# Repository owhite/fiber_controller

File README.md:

# fiber_controller

### **Collision protection**

* Raytools BM110/BM111 "Collision Protection" Kit

* BM111 have a specific internal magnetic sensor and a sacrificial ceramic assembly, but Raytools also offers an external 3D collision mount for high-end machines.  
* [Raytools TRA Nozzle Assembly](https://raytools.vn/product/raytools-original-tra-nozzle-assembly-for-bm111-bm110-laser-cutting-head/)  
* [Raytools 3d head sensor](https://www.amazon.com/Raytools-Head-Capacitive-Sensor-Connector/dp/B0FQ5VNJ7H?th=1) 
* Sacrificial Ceramic Rings If a full magnetic mount is too bulky for your Z-axis design, you should rely on the ceramic ring. For 1.5kW, this is the standard point of failure. [Original Raytools Ceramic Rings (AliExpress)](https://www.aliexpress.com/i/4000780398952.html)

FreeMascot 1064nm Safety Glasses

### **LinuxCNC stack**

* [QtPlasmaC](https://linuxcnc.org/docs/html/plasma/qtplasmac.html)  
* Mesa [7i96S](https://store.mesanet.com/index.php?route=product/product&product_id=374) (or 7i76E)  
* [THCAD-10](https://store.mesanet.com/index.php?route=product/product&product_id=127) height sensing

### **Controller box**

* [Raycus RFL-C1500 User Guide](https://en.raycuslaser.com/upload/20220324/1futhmi6h1r9g1vrto.pdf)  
* [Maxphotonics MFSC 1000W-1500W Manual](https://pdf.directindustry.com/pdf/maxphotonics-co-ltd/mfp-series-q-switched-pulse-fiber-laser-user-s-guide/157735-629681.html): If cloudraw source uses the Maxphotonics "G3" architecture, this manual provides the specific 8-bit power bus logic (Pins 1-8).

### **Laser side signal condition on DB-25**

* Modulation (Pin 19): Use an RS-422 Differential Receiver to maintain a crisp 20kHz pulse and block EMI over the long cable run.  
* Power Supply: Tap Pin 17 (+5V) on the laser's DB25 to power your buffer circuit (verify voltage with a multimeter first).  
* Grounding: Use Pin 25 (GND) as your logic common; ensure the cable shield is grounded at the laser end only.  
* Safety Isolation: Use Optoisolators for low-speed logic (Enable, Ready, Error) to protect the Mesa board from high-voltage faults.  
* Hardware: House the circuit in a shielded aluminum box mounted directly to the laser using a DB25 Male-to-Male gender changer.  
* Cable Quality: Deploy a double-shielded industrial DB25 cable (foil \+ braid) to act as a barrier against servo motor noise.

### **DIN rail systems**

* 24V Field Power system, Mean Well [SDR-120-24](https://mou.sr/4vt2Dxf)  
* General purpose relay [38.52.7.024.0050](https://www.digikey.com/en/products/detail/finder-relays-inc/38.52.7.024.0050/10055815) and socket 93.02.7.024  
* [Narrow Slot Wire Duct](https://google.com/search?q=\(1%22+W+x+3%22+H\)+-+Black+Narrow+Slot+Wire+Duct+6.5%27&prds=headlineOfferDocid%3A3394051378468670811%2Cproductid%3A3394051378468670811%2Cpvo%3A38%2Cpvt%3Ahg&ibp=oshop&pvo=38&opi=103135050&gl=US&hl=en&noiga=1)  
* [Push-In Terminal Blocks](https://google.com/search?q=10pcs/set+PT+2.5+Push-In+Din+Rail+Mounted+Terminal+Blocks+Spring+Screwless+Feed,+Size:+24,+Gray&prds=headlineOfferDocid%3A9693193005356797468%2Cproductid%3A9693193005356797468%2Cpvo%3A38%2Cpvt%3Ahg&ibp=oshop&pvo=38&opi=103135050&gl=US&hl=en&noiga=1)  
* [Grounding Terminal Blocks](https://google.com/search?q=Siemens+Ground+Terminal+Block&prds=catalogid%3A8330128584833181567%2Cgpcid%3A10243653714409647064%2CheadlineOfferDocid%3A14112956594196320175%2Cmid%3A576462728235596048%2Cproductid%3A7214032751195772387%2Cpvo%3A38%2Cpvt%3Ahg&ibp=oshop&pvo=38&opi=103135050&gl=US&hl=en&noiga=1)

### **Height sensing:**

* Preamplifier (BCL-AMP), Converts capacitance to 0-10V for the THCAD.  
* Ceramic Ring, Isolates the nozzle to act as a sensor.  
* Shielded Coax Cable, Connects nozzle to Preamplifier.  
* Isolated 24V PSU, Eliminates signal noise from the 1.5kW source.

### **Chiller**

* The  [**S\&A CWFL-1500**](https://google.com/search?q=S%26A+CWFL-1500+Industrial+Water+Chiller+For+1500W+Fiber+Laser+Cutting+Machine&prds=headlineOfferDocid%3A17375003498786172168%2Cproductid%3A17375003498786172168%2Cpvo%3A38%2Cpvt%3Ahg&ibp=oshop&pvo=38&opi=103135050&gl=US&hl=en&noiga=1) dual circuit chiller

### **Gas control**

* gas control [system](https://alleriastore.com/products/auxiliary-gas-control-system)

* [Travis Mitchell](https://www.patreon.com/DIYfiberlaser) patreon site has a bill of materials

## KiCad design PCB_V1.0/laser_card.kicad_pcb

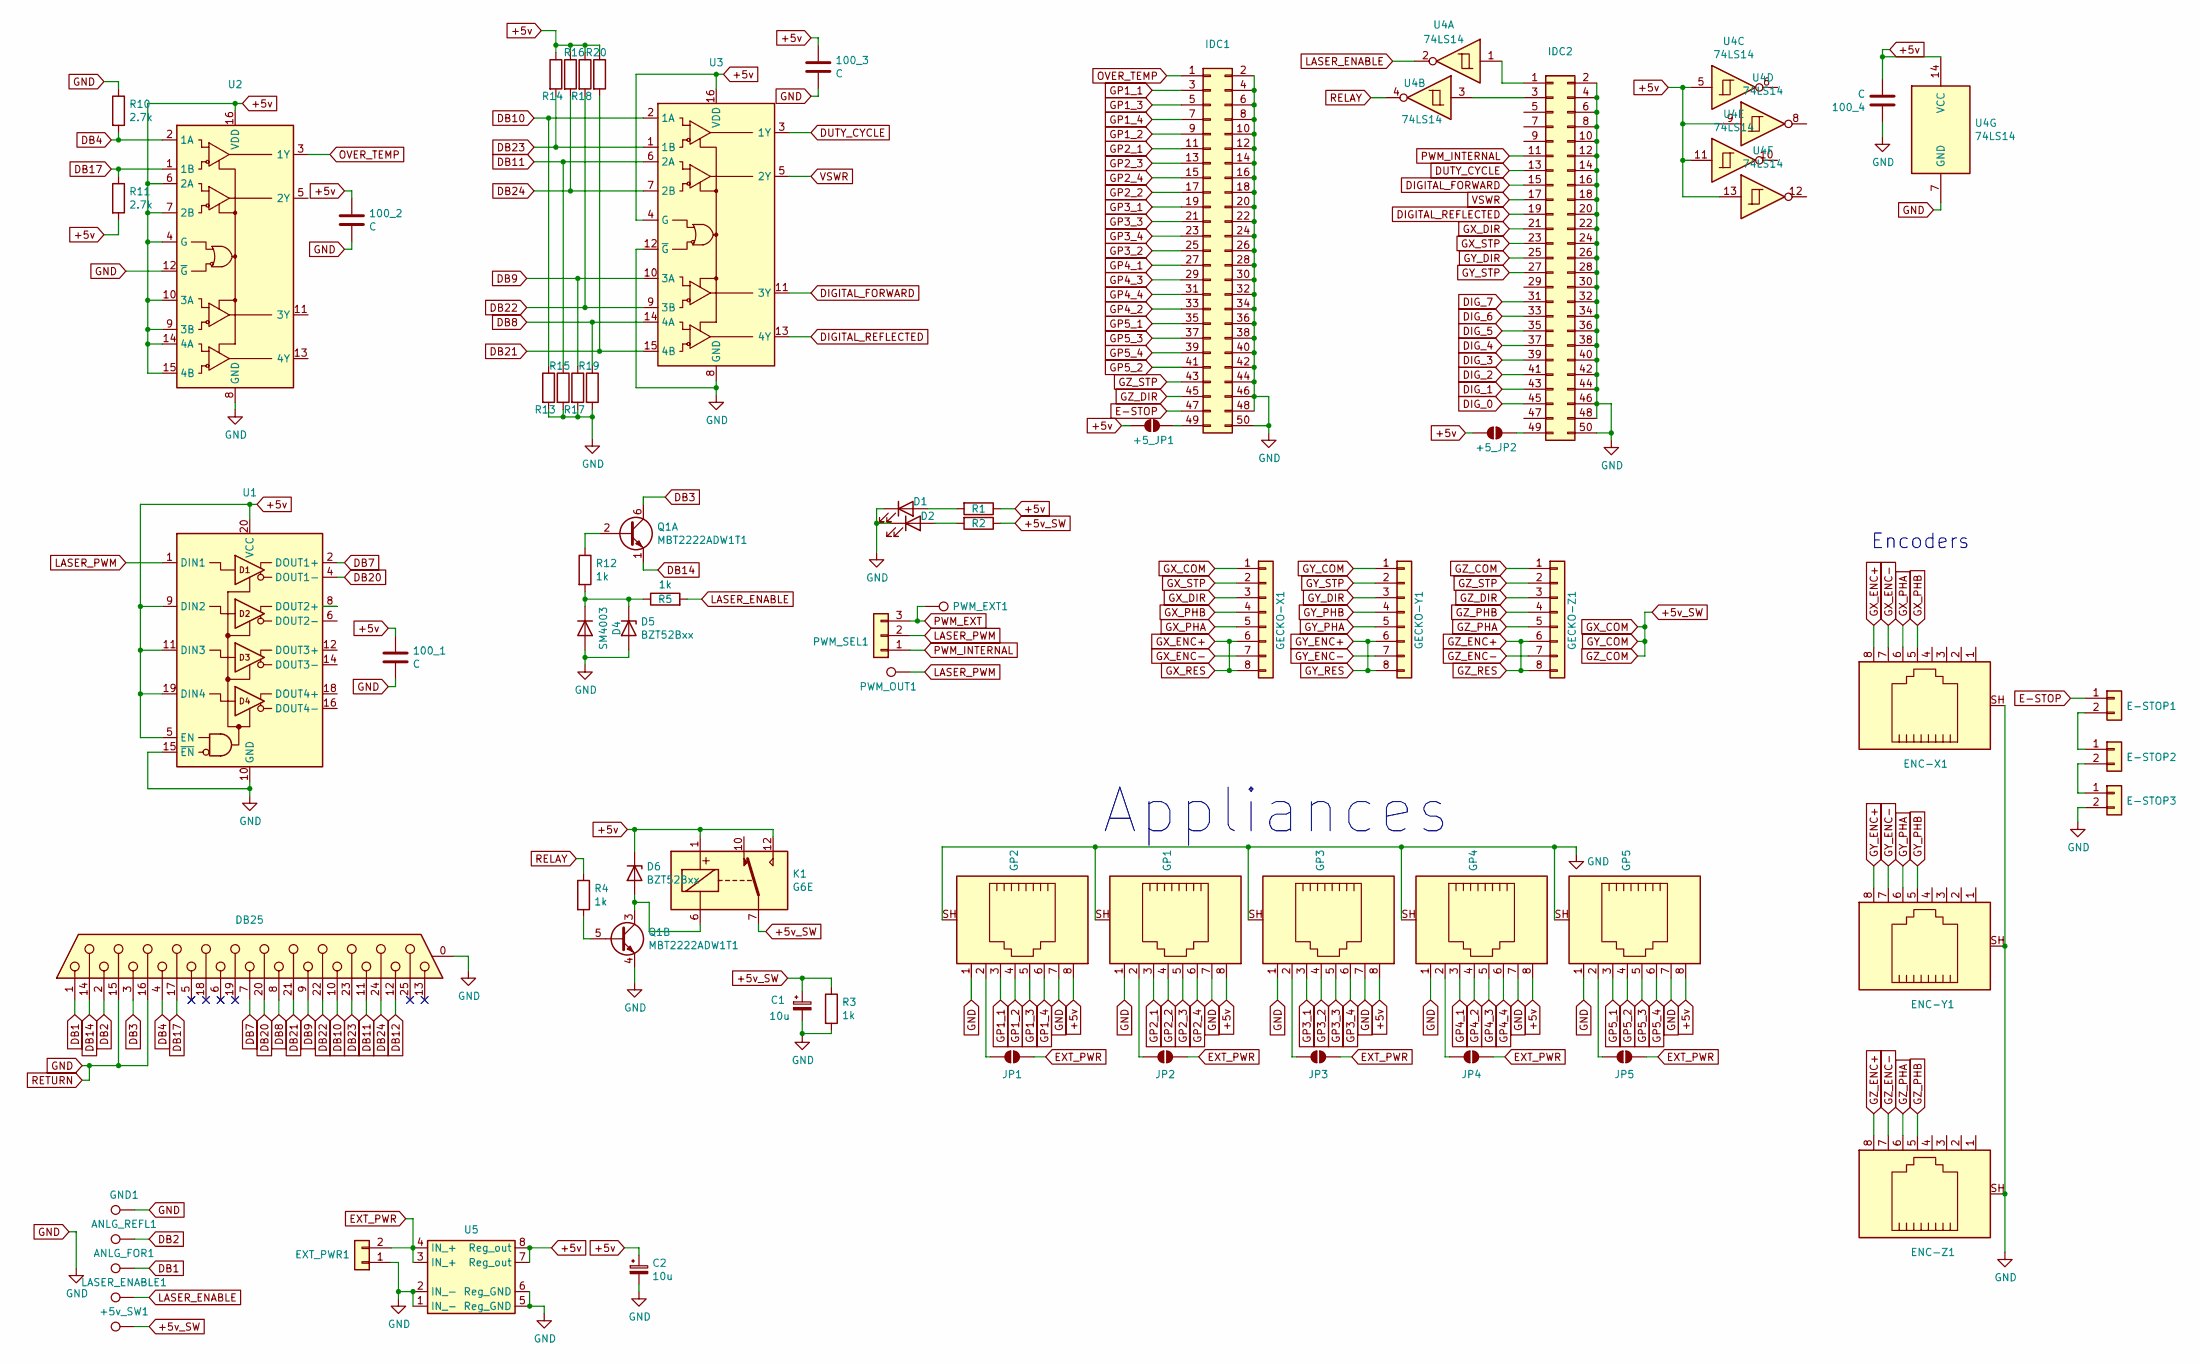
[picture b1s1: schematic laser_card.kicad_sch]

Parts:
100_1, 100_2, 100_3, 100_4: C; C_0805_2012Metric
+5_JP1, +5_JP2: SolderJumper_2_Open; SolderJumper-2_P1.3mm_Open_RoundedPad1.0x1.5mm
+5v_SW1: TestPoint; TestPoint_THTPad_2.0x2.0mm_Drill1.0mm
ANLG_FOR1: TestPoint; TestPoint_THTPad_2.0x2.0mm_Drill1.0mm
ANLG_REFL1: TestPoint; TestPoint_THTPad_2.0x2.0mm_Drill1.0mm
C1, C2: 10u; CP_Radial_D6.3mm_P2.50mm
D1, D2: LED; LED_0805_2012Metric
D4: SM4003; D_SOD-123F
D5, D6: BZT52Bxx; D_SOD-123
DB25: DB25_Female_MountingHoles; DSUB-25_Female_Vertical_P2.77x2.84mm_MountingHoles
E-STOP1, E-STOP2, E-STOP3: Conn_01x02; PinHeader_1x02_P2.54mm_Vertical
ENC-X1: RJ45_Shielded; my_RJ45_Amphenol
ENC-Y1: RJ45_Shielded; my_RJ45_Amphenol
ENC-Z1: RJ45_Shielded; my_RJ45_Amphenol
EXT_PWR1: Conn_01x02; PinHeader_1x02_P2.54mm_Vertical
GECKO-X1: molex; PinHeader_1x08_P2.54mm_Vertical
GECKO-Y1: molex; PinHeader_1x08_P2.54mm_Vertical
GECKO-Z1: molex; PinHeader_1x08_P2.54mm_Vertical
GND1: TestPoint; TestPoint_THTPad_2.0x2.0mm_Drill1.0mm
GP1, GP2, GP3, GP4, GP5: RJ45_Shielded; my_RJ45_Amphenol
IDC1, IDC2: Conn_02x25_Odd_Even; IDC-Header_2x25_P2.54mm_Vertical
JP1, JP2, JP3, JP4, JP5: SolderJumper_2_Open; SolderJumper-2_P1.3mm_Open_RoundedPad1.0x1.5mm
K1: G6E; Relay_SPDT_Omron_G6E
LASER_ENABLE1: TestPoint; TestPoint_THTPad_2.0x2.0mm_Drill1.0mm
PWM_EXT1: TestPoint; TestPoint_THTPad_2.0x2.0mm_Drill1.0mm
PWM_OUT1: TestPoint; TestPoint_THTPad_1.5x1.5mm_Drill0.7mm
PWM_SEL1: Conn_01x03; PinHeader_1x03_P2.54mm_Vertical
Q1: MBT2222ADW1T1; SOT-363_SC-70-6
R1, R2: 10k; R_0805_2012Metric
R3, R4, R5, R12: 1k; R_0805_2012Metric
R10, R11, R13, R14, R15, R16, R17, R18, R19, R20: 2.7k; R_0805_2012Metric
U1: SN75172_LINE_DRIVER; SOIC-20W_7.5x12.8mm_P1.27mm
U2, U3: SN75173_differential_line_receiver; SOIC-16_4.55x10.3mm_P1.27mm
U4: 74LS14; SOIC-14_3.9x8.7mm_P1.27mm
U5: my_buck_boost-Regulator_Switching; my_buck_boost

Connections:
+5v: 100_1.1, 100_2.1, 100_3.1, 100_4.2, +5_JP1.2 (B), +5_JP2.2 (B), C2.1, D6.1 (K), GP1.8, GP2.8, GP3.8, GP4.8, GP5.8, K1.1, K1.12, R1.1, R11.2, R14.1, R16.1, R18.1, R20.1, U1.5 (EN), U1.9 (DIN2), U1.11 (DIN3), U1.19 (DIN4), U1.20 (VCC), U2.4 (G), U2.6 (2A), U2.7 (2B), U2.9 (3B), U2.10 (3A), U2.14 (4A), U2.15 (4B), U2.16 (VDD), U3.4 (G), U3.16 (VDD), U4.5, U4.9, U4.11, U4.13, U4.14 (VCC), U5.7 (Reg_out), U5.8 (Reg_out)
+5v_SW: +5v_SW1.1, C1.1, GECKO-X1.1, GECKO-Y1.1, GECKO-Z1.1, K1.7, R2.1, R3.1
DB1: ANLG_FOR1.1, DB25.1
DB2: ANLG_REFL1.1, DB25.2
DB3: DB25.3, Q1.6 (C1)
DB4: DB25.4, R10.2, U2.2 (1A)
DB7: DB25.7, U1.2 (DOUT1+)
DB8: DB25.8, R19.1, U3.14 (4A)
DB9: DB25.9, R17.1, U3.10 (3A)
DB10: DB25.10, R13.1, U3.2 (1A)
DB11: DB25.11, R15.1, U3.6 (2A)
DB12: DB25.12
DB14: DB25.14, Q1.1 (E1)
DB17: DB25.17, R11.1, U2.1 (1B)
DB20: DB25.20, U1.4 (DOUT1-)
DB21: DB25.21, R20.2, U3.15 (4B)
DB22: DB25.22, R18.2, U3.9 (3B)
DB23: DB25.23, R14.2, U3.1 (1B)
DB24: DB25.24, R16.2, U3.7 (2B)
DIGITAL_FORWARD: IDC2.15, U3.11 (3Y)
DIGITAL_REFLECTED: IDC2.19, U3.13 (4Y)
DIG_0: IDC2.45
DIG_1: IDC2.43
DIG_2: IDC2.41
DIG_3: IDC2.39
DIG_4: IDC2.37
DIG_5: IDC2.35
DIG_6: IDC2.33
DIG_7: IDC2.31
DUTY_CYCLE: IDC2.13, U3.3 (1Y)
E-STOP: E-STOP1.1, IDC1.47
EXT_PWR: EXT_PWR1.2, JP1.2 (B), JP2.2 (B), JP3.2 (B), JP4.2 (B), JP5.2 (B), U5.3 (IN_+), U5.4 (IN_+)
GND: 100_1.2, 100_2.2, 100_3.2, 100_4.1, C1.2, C2.2, D1.1 (K), D2.1 (K), D4.2 (A), D5.2 (A), DB25.0 (PAD), DB25.15, DB25.16, E-STOP3.2, ENC-X1.SH, ENC-Y1.SH, ENC-Z1.SH, EXT_PWR1.1, GND1.1, GP1.1, GP1.7, GP1.SH, GP2.1, GP2.7, GP2.SH, GP3.1, GP3.7, GP3.SH, GP4.1, GP4.7, GP4.SH, GP5.1, GP5.7, GP5.SH, IDC1.2, IDC1.4, IDC1.6, IDC1.8, IDC1.10, IDC1.12, IDC1.14, IDC1.16, IDC1.18, IDC1.20, IDC1.22, IDC1.24, IDC1.26, IDC1.28, IDC1.30, IDC1.32, IDC1.34, IDC1.36, IDC1.38, IDC1.40, IDC1.42, IDC1.44, IDC1.46, IDC1.48, IDC1.50, IDC2.2, IDC2.4, IDC2.6, IDC2.8, IDC2.10, IDC2.12, IDC2.14, IDC2.16, IDC2.18, IDC2.20, IDC2.22, IDC2.24, IDC2.26, IDC2.28, IDC2.30, IDC2.32, IDC2.34, IDC2.36, IDC2.38, IDC2.40, IDC2.42, IDC2.44, IDC2.46, IDC2.48, IDC2.50, Q1.4 (E2), R3.2, R10.1, R13.2, R15.2, R17.2, R19.2, U1.10 (GND), U1.15 (~EN), U2.8 (GND), U2.12 (~G), U3.8 (GND), U3.12 (~G), U4.7 (GND), U5.1 (IN_-), U5.2 (IN_-), U5.5 (Reg_GND), U5.6 (Reg_GND)
GP1_1: GP2.3, IDC1.3
GP1_2: GP2.4, IDC1.9
GP1_3: GP2.5, IDC1.5
GP1_4: GP2.6, IDC1.7
GP2_1: GP1.3, IDC1.11
GP2_2: GP1.4, IDC1.17
GP2_3: GP1.5, IDC1.13
GP2_4: GP1.6, IDC1.15
GP3_1: GP3.3, IDC1.19
GP3_2: GP3.4, IDC1.25
GP3_3: GP3.5, IDC1.21
GP3_4: GP3.6, IDC1.23
GP4_1: GP4.3, IDC1.27
GP4_2: GP4.4, IDC1.33
GP4_3: GP4.5, IDC1.29
GP4_4: GP4.6, IDC1.31
GP5_1: GP5.3, IDC1.35
GP5_2: GP5.4, IDC1.41
GP5_3: GP5.5, IDC1.37
GP5_4: GP5.6, IDC1.39
GX_DIR: GECKO-X1.3, IDC2.21
GX_ENC+: ENC-X1.8, GECKO-X1.6, GECKO-X1.8
GX_ENC-: ENC-X1.7, GECKO-X1.7
GX_PHA: ENC-X1.6, GECKO-X1.5
GX_PHB: ENC-X1.5, GECKO-X1.4
GX_STP: GECKO-X1.2, IDC2.23
GY_DIR: GECKO-Y1.3, IDC2.25
GY_ENC+: ENC-Y1.8, GECKO-Y1.6, GECKO-Y1.8
GY_ENC-: ENC-Y1.7, GECKO-Y1.7
GY_PHA: ENC-Y1.6, GECKO-Y1.5
GY_PHB: ENC-Y1.5, GECKO-Y1.4
GY_STP: GECKO-Y1.2, IDC2.27
GZ_DIR: GECKO-Z1.3, IDC1.45
GZ_ENC+: ENC-Z1.8, GECKO-Z1.6, GECKO-Z1.8
GZ_ENC-: ENC-Z1.7, GECKO-Z1.7
GZ_PHA: ENC-Z1.6, GECKO-Z1.5
GZ_PHB: ENC-Z1.5, GECKO-Z1.4
GZ_STP: GECKO-Z1.2, IDC1.43
LASER_ENABLE: LASER_ENABLE1.1, R5.2, U4.2
LASER_PWM: PWM_OUT1.1, PWM_SEL1.2, U1.1 (DIN1)
unnamed: +5_JP1.1 (A), IDC1.49
unnamed: +5_JP2.1 (A), IDC2.49
unnamed: D1.2 (A), R1.2
unnamed: D2.2 (A), R2.2
unnamed: D4.1 (K), D5.1 (K), R5.1, R12.2
unnamed: D6.2 (A), K1.6, Q1.3 (C2)
unnamed: E-STOP1.2, E-STOP2.1
unnamed: E-STOP2.2, E-STOP3.1
unnamed: GP1.2, JP2.1 (A)
unnamed: GP2.2, JP1.1 (A)
unnamed: GP3.2, JP3.1 (A)
unnamed: GP4.2, JP4.1 (A)
unnamed: GP5.2, JP5.1 (A)
unnamed: IDC2.1, U4.1
unnamed: IDC2.3, U4.3
unnamed: Q1.2 (B1), R12.1
unnamed: Q1.5 (B2), R4.2
OVER_TEMP: IDC1.1, U2.3 (1Y)
PWM_EXT: PWM_EXT1.1, PWM_SEL1.3
PWM_INTERNAL: IDC2.11, PWM_SEL1.1
RELAY: R4.1, U4.4
VSWR: IDC2.17, U3.5 (2Y)

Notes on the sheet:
Encoders
Appliances

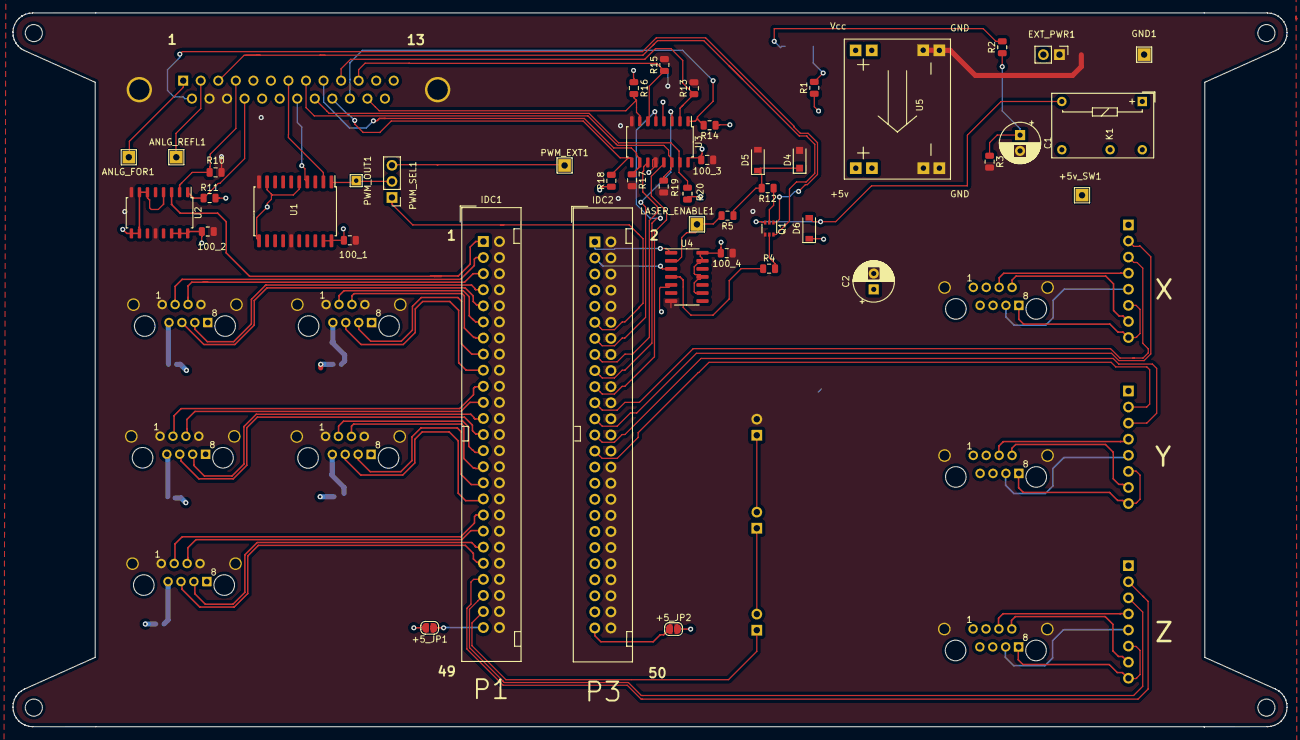
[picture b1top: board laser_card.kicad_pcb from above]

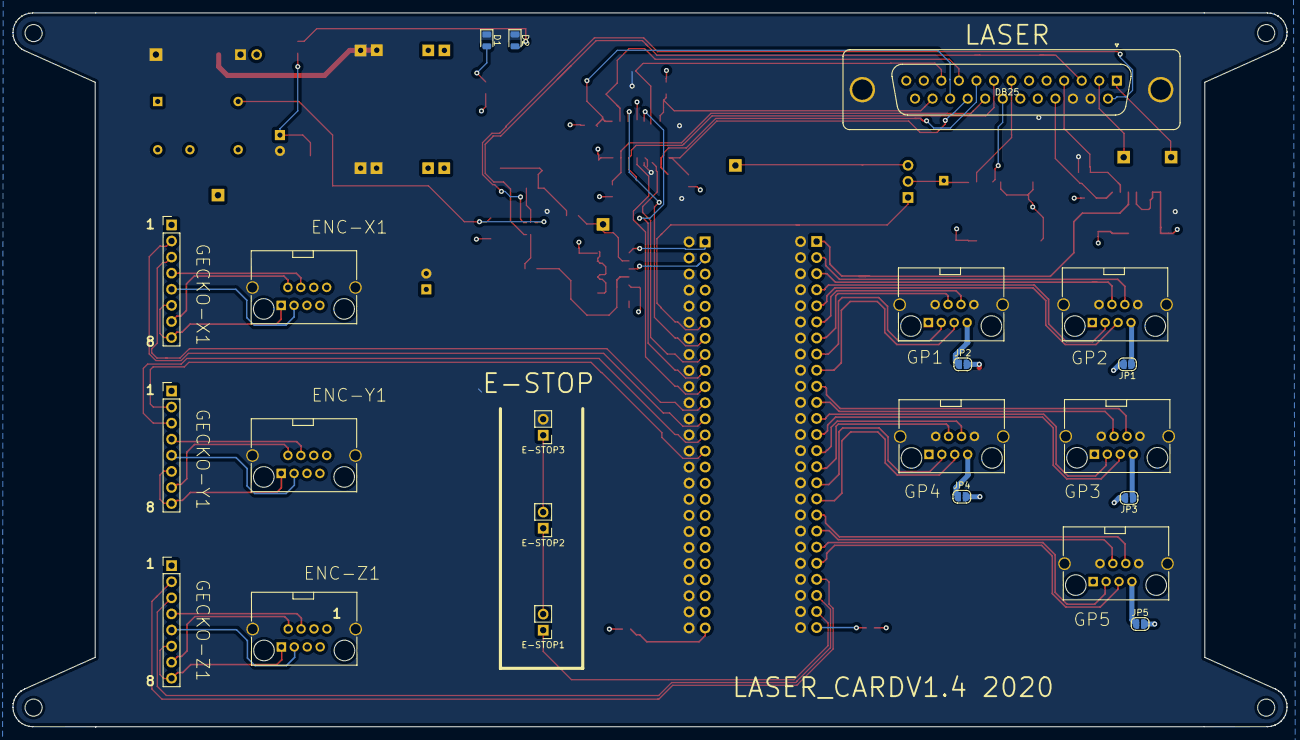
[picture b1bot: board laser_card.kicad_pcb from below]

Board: 4 copper layers, 201.2 x 112.7 mm, 67 parts (22 on the bottom side), 86 nets.

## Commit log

2026-04-13 first init
2026-04-13 edited readme
2026-04-14 controller_box work
